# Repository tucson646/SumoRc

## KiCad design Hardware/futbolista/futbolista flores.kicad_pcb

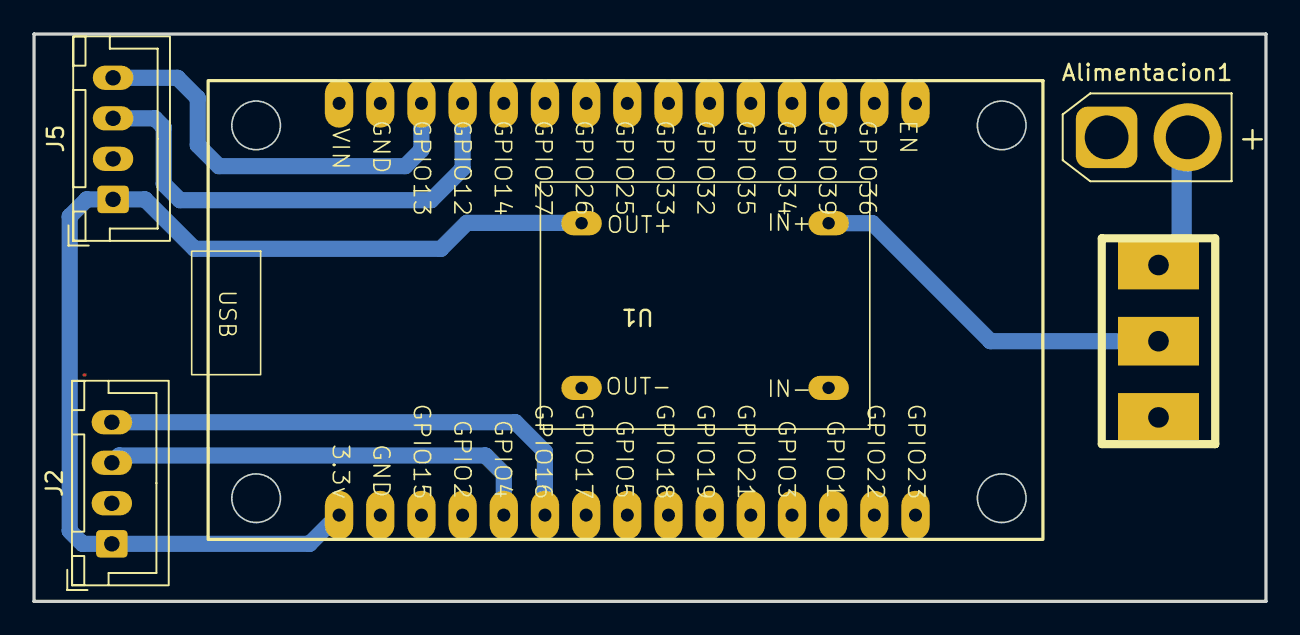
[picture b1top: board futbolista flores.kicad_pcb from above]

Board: 2 copper layers, 76.0 x 35.0 mm, 6 parts (0 on the bottom side), 8 nets.

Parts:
Alimentacion1: TB_1X2; AMASS_XT30U-M_1x02_P5.0mm_Vertical
J2: BTS-1; JST_XH_B4B-XH-A_1x04_P2.50mm_Vertical
J5: BTS-2; JST_XH_B4B-XH-A_1x04_P2.50mm_Vertical
SW1: SW_DPST_x2; SW_SPDT_TH_Vertical
U1: ESP32_30pin
stepdown1: STEPDOWN

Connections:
+5V: J2.1, J5.1, U1.16 (3.3v), stepdown1.2 (out+)
GND: Alimentacion1.1, J2.2, J5.2, U1.2 (GND), U1.17 (GND), stepdown1.1 (out-), stepdown1.3 (in-)
INA1: J2.3, U1.20 (GPIO4)
INA2: J5.4, U1.3 (GPIO13)
INB1: J2.4, U1.21 (GPIO16)
INB2: J5.3, U1.4 (GPIO12)
VCC: Alimentacion1.2, SW1.1 (A)
VCC1: SW1.2 (B), stepdown1.4 (in+)

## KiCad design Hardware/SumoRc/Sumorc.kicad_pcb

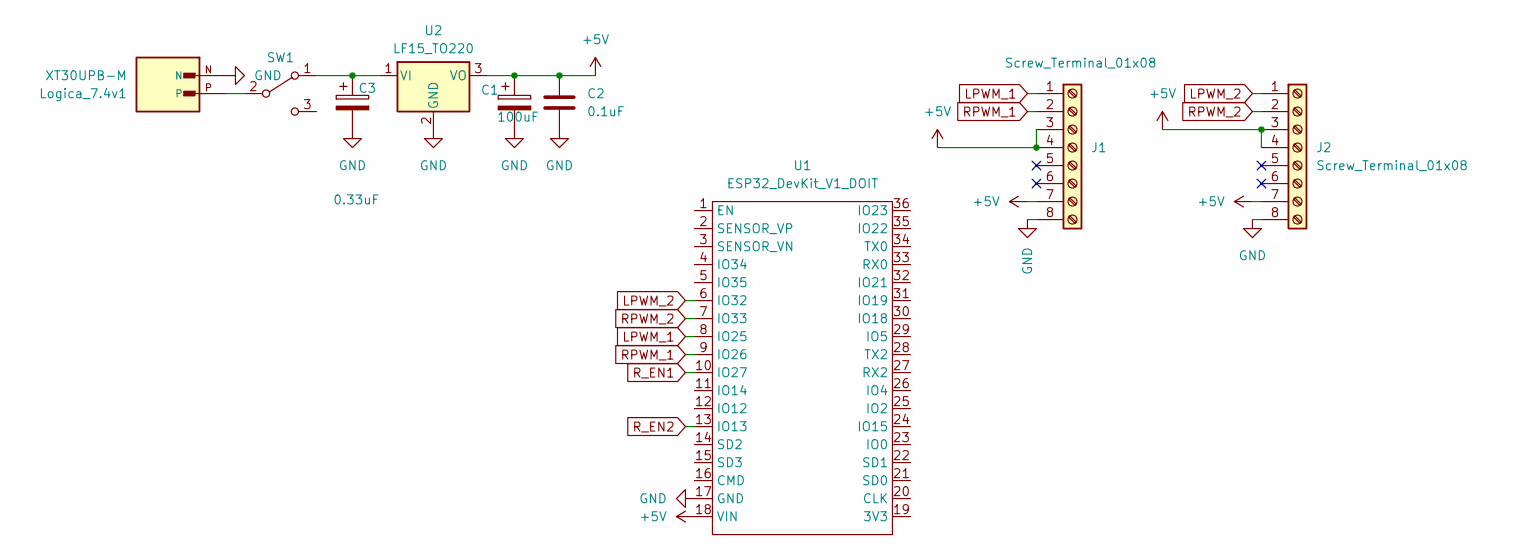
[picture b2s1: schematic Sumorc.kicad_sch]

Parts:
C1: 100uF; CP_Radial_D5.0mm_P2.50mm
C2: 0.1uF; C_0805_2012Metric_Pad1.18x1.45mm_HandSolder
C3: 0.33uF; CP_Radial_D5.0mm_P2.50mm
J1, J2: Screw_Terminal_01x08; IDC-Header_2x04_P2.54mm_Vertical
Logica_7.4v1: XT30UPB-M; AMASS_XT30UPB-M
SW1: SW_SPDT; SW_SPDT_TH_Vertical
U1: ESP32_DevKit_V1_DOIT; ESP32_DEVKIT_V1_DOIT
U2: LF15_TO220; TO-263-3_TabPin2

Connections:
+5V: C1.1, C2.1, J1.3, J1.4, J1.7, J2.3, J2.4, J2.7, U1.18 (VIN), U2.3 (VO)
GND: C1.2, C2.2, C3.2, J1.8, J2.8, Logica_7.4v1.N, U1.17 (GND), U2.2 (GND)
LPWM_1: J1.1, U1.8 (IO25)
LPWM_2: J2.1, U1.6 (IO32)
unnamed: C3.1, SW1.1 (A), U2.1 (VI)
unnamed: Logica_7.4v1.P, SW1.2 (B)
RPWM_1: J1.2, U1.9 (IO26)
RPWM_2: J2.2, U1.7 (IO33)
R_EN1: U1.10 (IO27)
R_EN2: U1.13 (IO13)

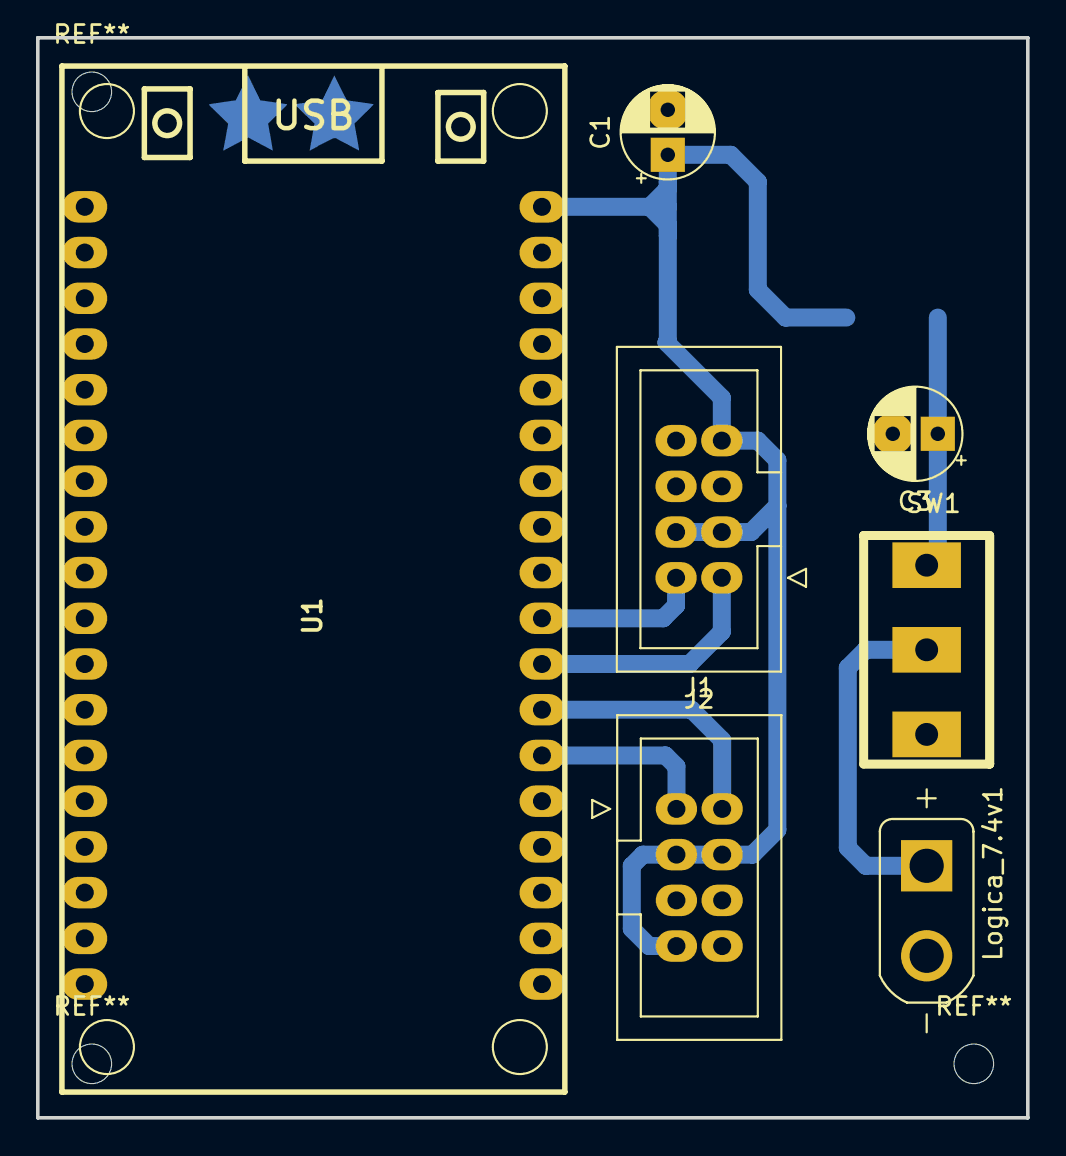
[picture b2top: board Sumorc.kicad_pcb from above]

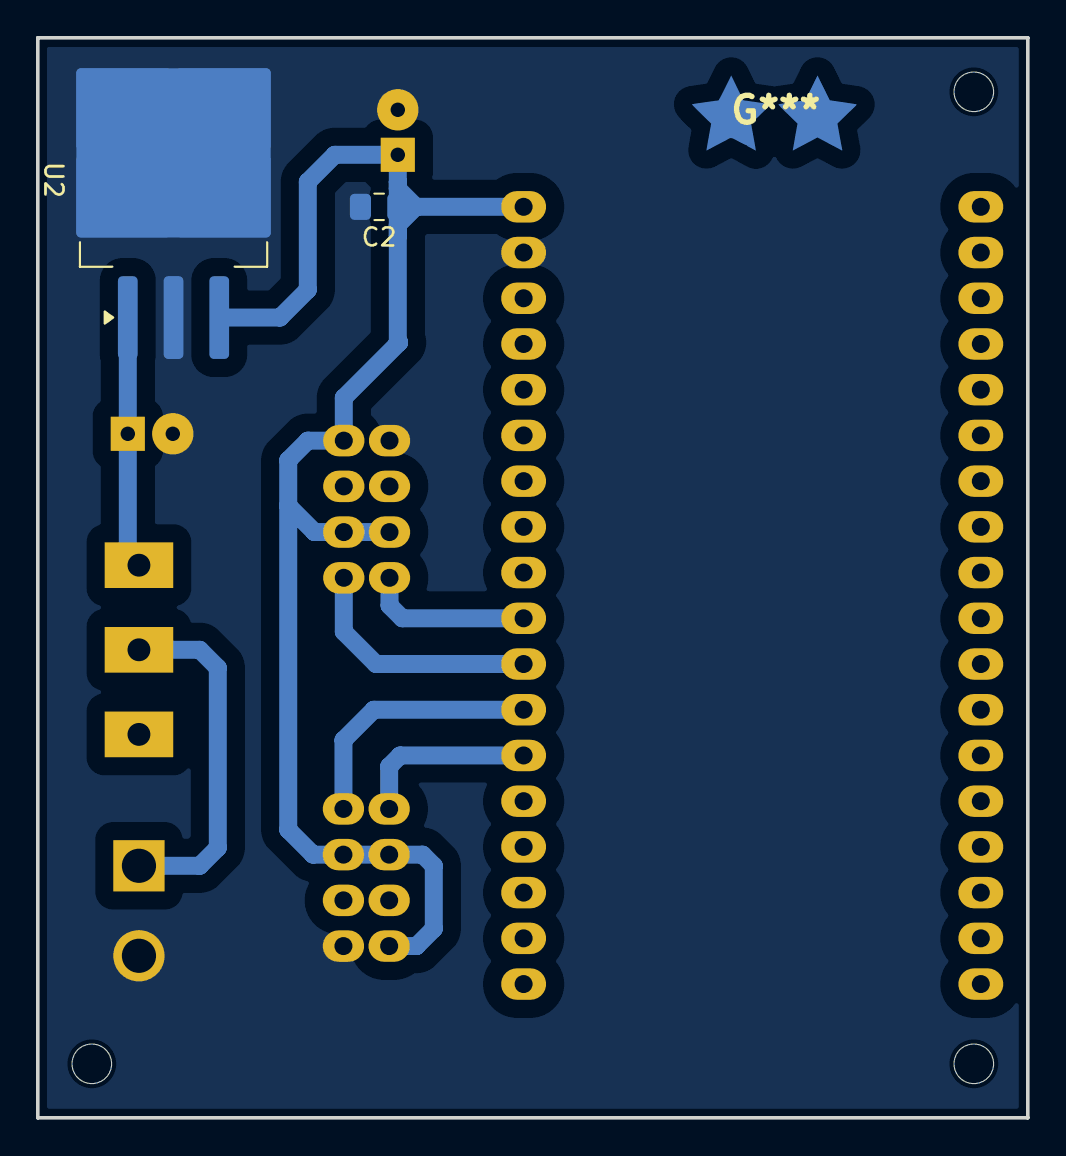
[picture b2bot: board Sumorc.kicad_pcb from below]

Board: 2 copper layers, 55.0 x 60.0 mm, 9 parts (2 on the bottom side), 8 nets.

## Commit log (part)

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2026-05-04 se creo el repositorio
2026-05-05 se actualizo el esquematico y pcb
2026-05-11 add folders
2026-05-11 deleted
2026-05-18 update Hardware
2026-05-20 se actualizo el PCB
2026-06-02 actualizacion
